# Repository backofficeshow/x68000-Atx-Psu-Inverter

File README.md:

# x68000-Atx-Psu-Inverter
You will want to build this to convert your Sharp x68000 to be able to use a modern ATX PSU

Refer to YouTube video on more details: https://youtu.be/1u4BrF8XW6E

You need only 4 connections to this, 5v (from the permament standby logic circuit), GND, the PS-ON From the Sharp x68000 and the PS-ON from the ATX PSU

Note: If you are removing the ATX cables completely, ensure that you solder 3v3 sense wire on your PSU (this usually goes to the ATX connector and is spliced to the 3v3 line) directly to the 3v3 on the ATX PSU itself, otherwise the PSU will shut down after a second when you power it up.

Have fun and be careful!!

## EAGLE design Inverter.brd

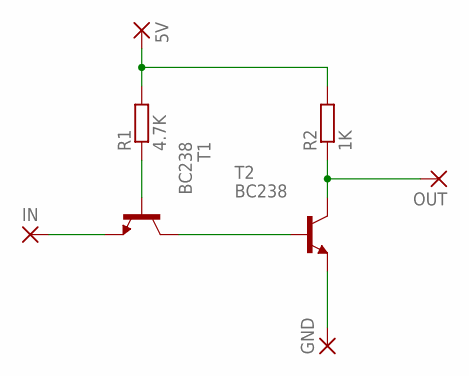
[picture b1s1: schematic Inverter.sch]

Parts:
5V: 2,54/0,8
GND: 2,54/0,8
IN: 2,54/0,8
OUT: 2,54/0,8
R1: 4.7K; 0204/7
R2: 1K; 0204/7
T1, T2: BC238; TO92

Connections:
GND: GND.1, T2.1 (E)
unnamed: IN.1, T1.1 (E)
unnamed: R1.1, T1.2 (B)
unnamed: T1.3 (C), T2.2 (B)
unnamed: OUT.1, R2.1, T2.3 (C)
unnamed: 5V.1, R1.2, R2.2

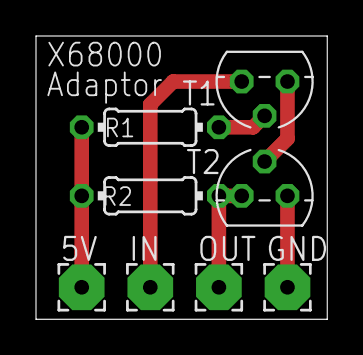
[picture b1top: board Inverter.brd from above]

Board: 2 copper layers, 16.2 x 15.7 mm, 8 parts (0 on the bottom side), 6 nets.

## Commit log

2019-03-17 Initial Commit!
